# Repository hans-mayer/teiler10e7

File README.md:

# teiler10e7

( english: divider by 10^7 )

This is part of a NTP project.

It contains a PCB ( printed circuit board ) designed with EAGLE 7.7.0

The NTP server exist of the following components

* a Banana Pi M1 with GNU/Linux 3.4.113
* a rubidium 10 MHz frequency standard
* a frequency divider by 10000000 to get a 1PPS ( this hardware )

This PCB has 2 connectors.

* JP1 connected to the GPIO of the Banana Pi
* JP2 connected to the rubidium 10 MHz frequency

Connector JP1

* GPIO0 pin 11 BCM17 - input for 1PPS
* GPIO2 pin 13 BCM27 - output to insert pulses
* GPIO3 pin 15 BCM22 - output for delay
* GND - pin 6,9,14,25
* Vcc +3.3 V - pin 1,17

The 10 MHz signal - a sine wave with about 10 Vss - is converted into TTL with a schmitt trigger 74HC132D. 7 stages of decade counters (74HT390D) will produce a 1PPS signal. After the first stage (1 MHz) there is a NAND and a X-OR. This allows to adjust the timer especially after boot. The NAND (IC3D) is connected with pin 12 to GPIO3 and offers the possibility the strip off some pulses. This results in a delay. With the X-OR (IC4A) additional pulses can be inserted on pin 1. It's connected to GPIO2.

To manage inserting and stripping off pulses I wrote a small C program which can be found here: https://github.com/hans-mayer/wiringPin

A detailed description will come soon.

This is the finished PCB (component site) <br>
The soldering site has only the connector JP1

This is the same but on my breadboard before I developed the PCB with Eagle. 

See also:

* <a href="http://blog.mayer.tv/2017/06/11/stratum-0-server.html" target="_blank">Stratum-1 NTP Server with rubidium source</a>
* <a href="http://blog.mayer.tv/2016/01/08/bananapi-gpio-wiringbp.html" target="_blank">Banana Pi - GPIO - WiringBP</a>
* <a href="http://blog.mayer.tv/2016/01/01/cd47hc4059.html" target="_blank">failed first attempt with 74HC4059

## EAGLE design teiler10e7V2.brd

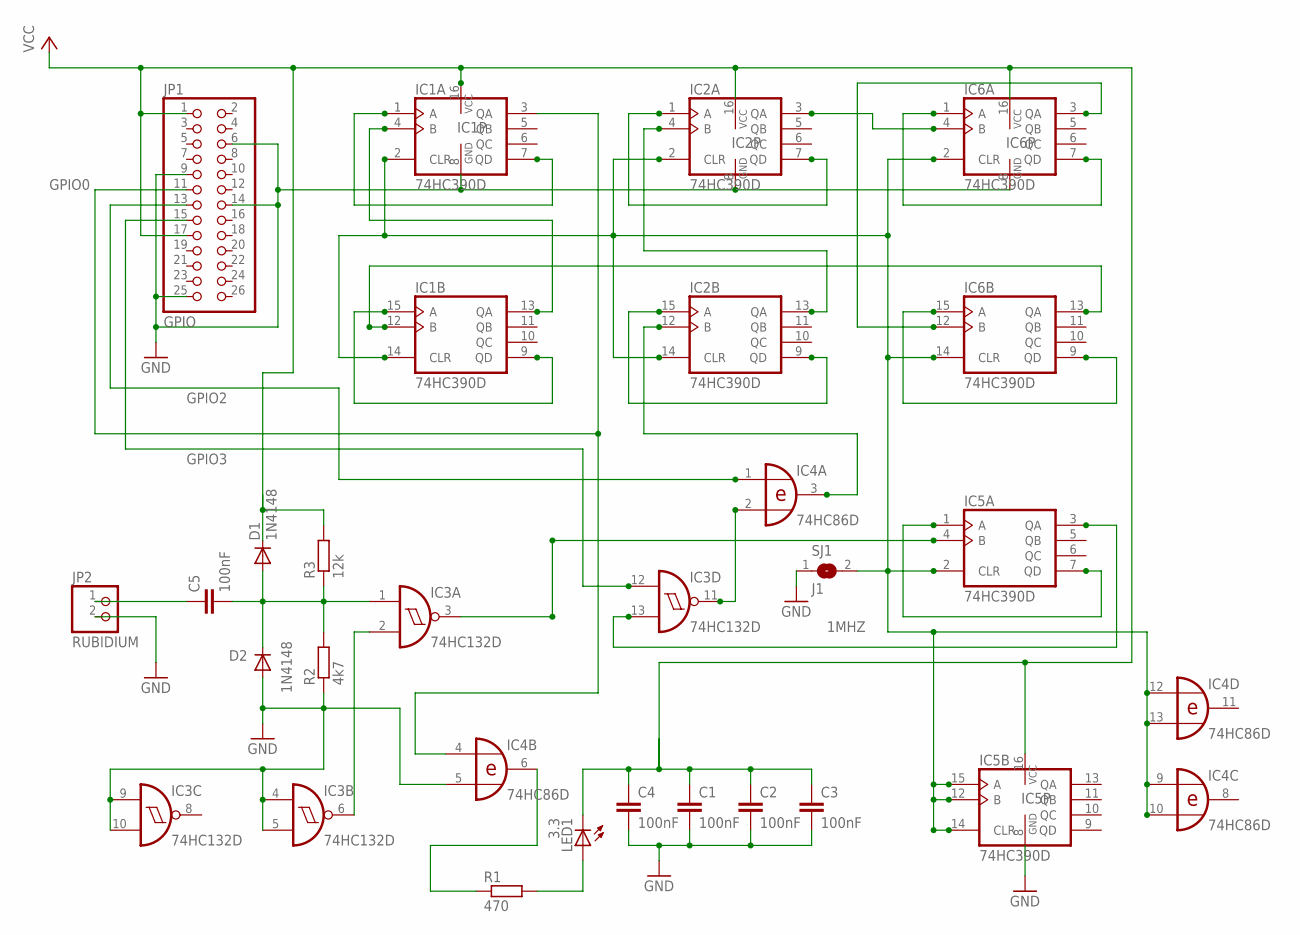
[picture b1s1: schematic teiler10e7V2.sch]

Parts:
C1, C2, C3, C4, C5: 100nF; C025-025X050
D1, D2: 1N4148; DO35-7
IC1, IC2, IC5, IC6: 74HC390D; SO16
IC3: 74HC132D; SO14
IC4: 74HC86D; SO14
JP1: GPIO; 2X13
JP2: RUBIDIUM; 1X02/90
LED1: 3.3; LED3MM
R1: 470; 0207/10
R2: 4k7; 0207/10
R3: 12k; 0207/10
SJ1: J1; SJW

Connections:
1KHZ: IC6.3 (QA), IC6.12 (B)
1MHZ: IC3.13 (I1), IC5.3 (QA)
10KHZ: IC2.3 (QA), IC6.4 (B)
100KHZ: IC2.4 (B), IC2.13 (QA)
CLR: IC1.2 (CLR), IC1.14 (CLR), IC2.2 (CLR), IC2.14 (CLR), IC4.9 (I0), IC4.10 (I1), IC4.12 (I0), IC4.13 (I1), IC5.2 (CLR), IC5.12 (B), IC5.14 (CLR), IC5.15 (A), IC6.2 (CLR), IC6.14 (CLR), SJ1.2
GND: C1.2, C2.2, C3.2, C4.2, D2.A, IC1.8 (GND), IC2.8 (GND), IC3.4 (I0), IC3.5 (I1), IC3.7 (GND), IC3.9 (I0), IC3.10 (I1), IC4.5 (I1), IC4.7 (GND), IC5.8 (GND), IC6.8 (GND), JP1.6, JP1.9, JP1.14, JP1.25, JP2.2, R2.1, SJ1.1
GPIO0: IC1.3 (QA), IC4.4 (I0), JP1.11
GPIO2: IC4.1 (I0), JP1.13
GPIO3: IC3.12 (I0), JP1.15
unnamed: IC1.1 (A), IC1.7 (QD)
unnamed: IC2.1 (A), IC2.7 (QD)
unnamed: IC1.9 (QD), IC1.15 (A)
unnamed: IC2.9 (QD), IC2.15 (A)
unnamed: IC5.1 (A), IC5.7 (QD)
unnamed: IC1.12 (B), IC6.13 (QA)
unnamed: IC2.12 (B), IC4.3 (O)
unnamed: IC1.4 (B), IC1.13 (QA)
unnamed: C5.1, JP2.1
unnamed: IC4.6 (O), R1.1
unnamed: IC3.11 (O), IC4.2 (I1)
unnamed: IC6.1 (A), IC6.7 (QD)
unnamed: IC6.9 (QD), IC6.15 (A)
unnamed: IC3.2 (I1), IC3.6 (O)
unnamed: IC3.3 (O), IC5.4 (B)
unnamed: LED1.A, R1.2
RUBIDIUM: C5.2, D1.A, D2.C, IC3.1 (I0), R2.2, R3.1
VCC: C1.1, C2.1, C3.1, C4.1, D1.C, IC1.16 (VCC), IC2.16 (VCC), IC3.14 (VCC), IC4.14 (VCC), IC5.16 (VCC), IC6.16 (VCC), JP1.1, JP1.17, LED1.K (C), R3.2

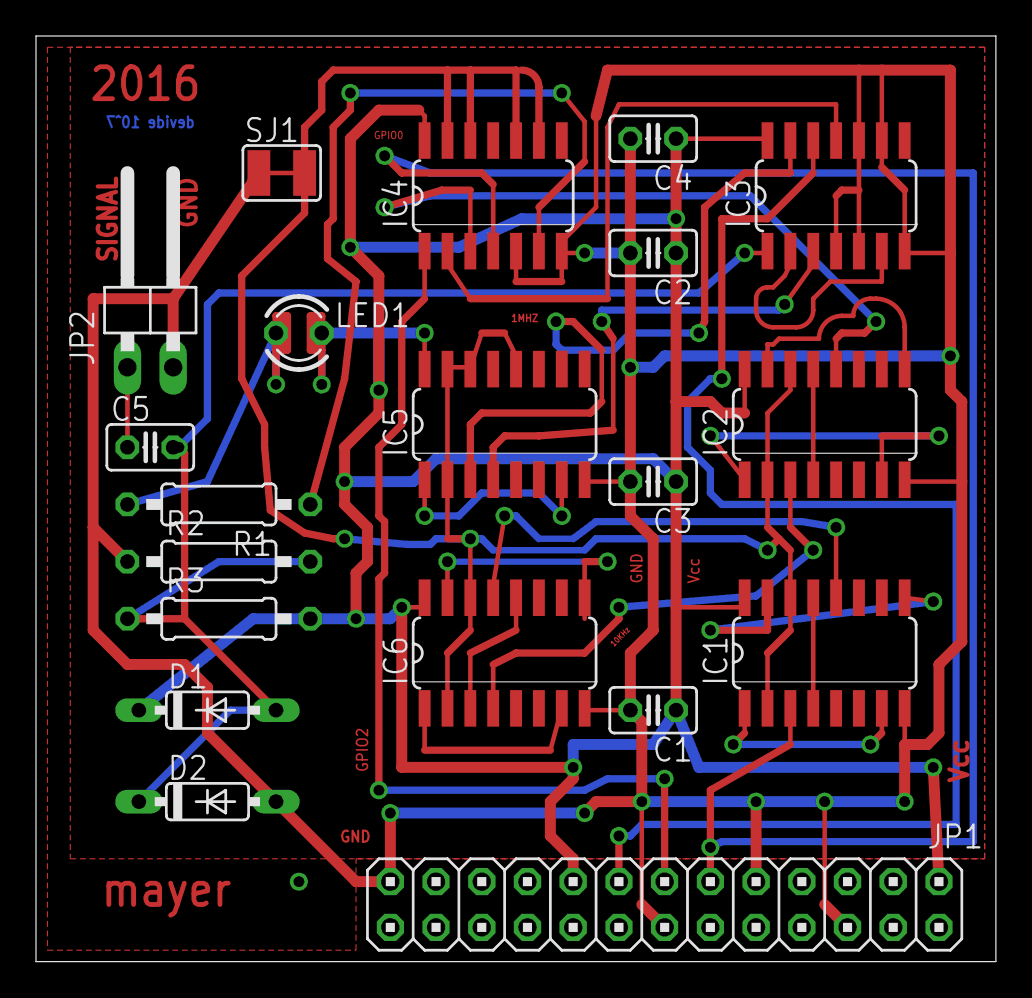
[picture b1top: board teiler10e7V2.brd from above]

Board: 2 copper layers, 53.3 x 51.4 mm, 20 parts (0 on the bottom side), 27 nets.

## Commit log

2017-01-13 circuitdiagram.png , deleting old version 2
2017-01-29 eagle.epf
2017-01-29 a more detailed description
2017-05-07 pcb_teiler.png finished soldered
2017-05-07 readme pcb_teiler.png finished soldered
2017-05-31 link to wiringPin
2017-06-15 README.md - some links
2017-06-15 README.md - ext link no {:target="_blank"}
2017-06-17 breadboard.png
